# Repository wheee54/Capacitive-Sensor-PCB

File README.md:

# Capacitive-Sensor-PCB
Demo Project for NUS Shape of Sound Class

This project is based on the (1) USBMIDI library for Arduino by Blokas [Link: https://github.com/BlokasLabs/USBMIDI] and (2) Electronics as Material Touch Sensor example by clementzheng [Link: https://github.com/clementzheng/Electronics-As-Material]

## Hardware

The dreamer nano microcontroller [Link: https://www.dfrobot.com/product-786.html] is used as a midi device and needs to be connected to a VST via USB.
The PCB files have headers for the microcontoller and also features a built in touch sensor into the top copper layer.

## Code

The .h files required should be downloaded before use.
It is recommended to uncomment the Serial.print lines to read and tune capVal for your specific design.

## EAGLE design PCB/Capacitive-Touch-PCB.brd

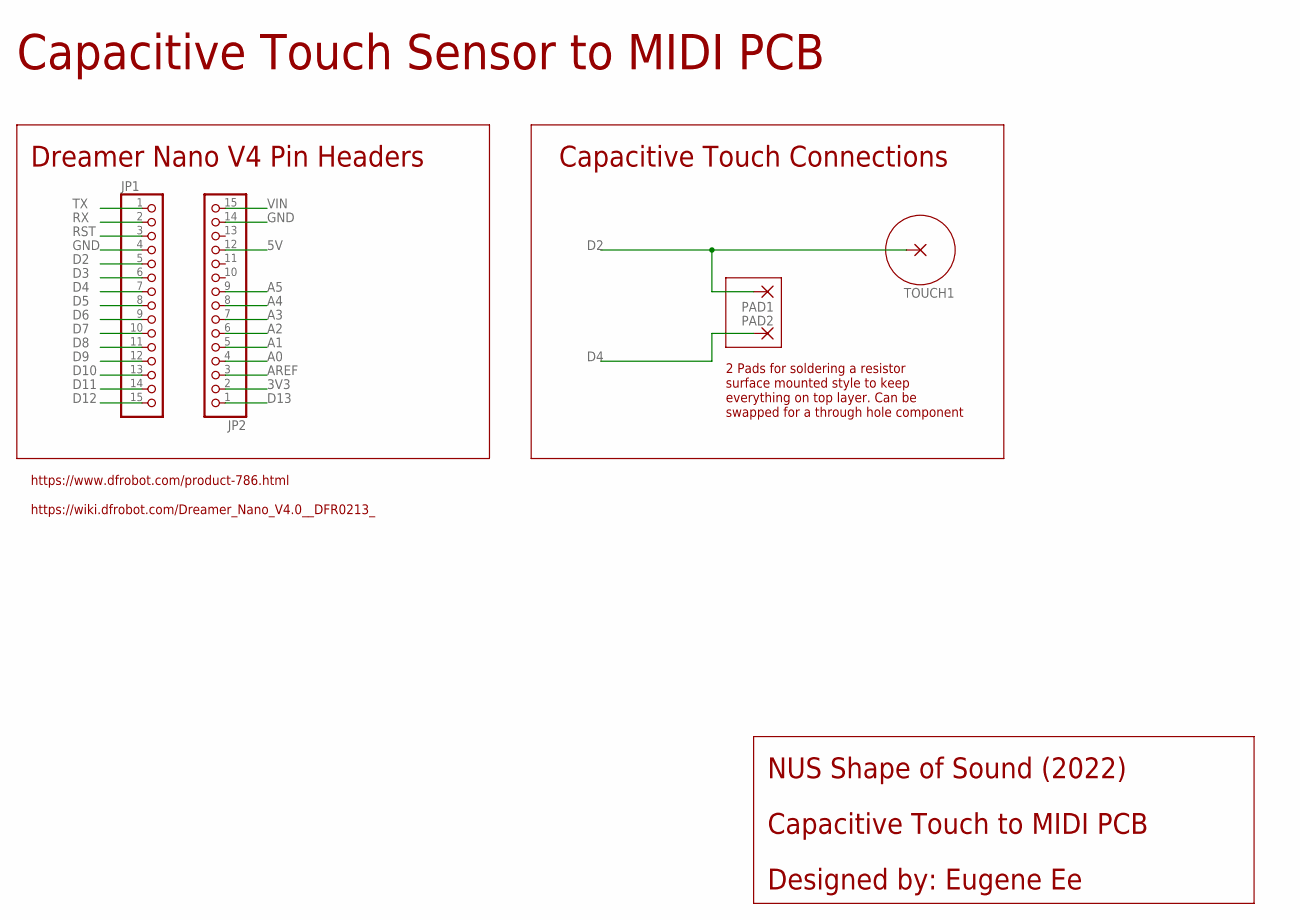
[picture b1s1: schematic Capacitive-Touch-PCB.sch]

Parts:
JP1, JP2: PINHD-1X15; 1X15
PAD1, PAD2: SMD5; SMD2,54-5,08
TOUCH1: SMD5; SMD2,54-5,08

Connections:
3V3: JP2.2
5V: JP2.12
A0: JP2.4
A1: JP2.5
A2: JP2.6
A3: JP2.7
A4: JP2.8
A5: JP2.9
AREF: JP2.3
D2: JP1.5, PAD1.1, TOUCH1.1
D3: JP1.6
D4: JP1.7, PAD2.1
D5: JP1.8
D6: JP1.9
D7: JP1.10
D8: JP1.11
D9: JP1.12
D10: JP1.13
D11: JP1.14
D12: JP1.15
D13: JP2.1
GND: JP1.4, JP2.14
RST: JP1.3
RX: JP1.2
TX: JP1.1
VIN: JP2.15

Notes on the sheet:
Dreamer Nano V4 Pin Headers
Capacitive Touch Sensor to MIDI PCB
2 Pads for soldering a resistor surface mounted style to keep everything on top layer. Can be swapped for a through hole component
Capacitive Touch Connections
Capacitive Touch to MIDI PCB
Designed by: Eugene Ee
NUS Shape of Sound (2022)
https://www.dfrobot.com/product-786.html https://wiki.dfrobot.com/Dreamer_Nano_V4.0__DFR0213_

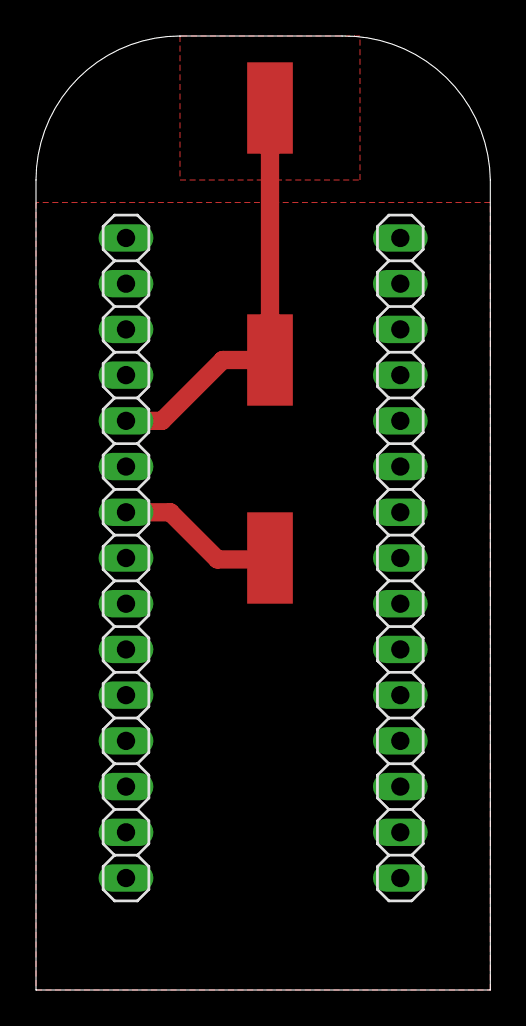
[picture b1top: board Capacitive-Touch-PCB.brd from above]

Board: 2 copper layers, 25.2 x 53.0 mm, 5 parts (0 on the bottom side), 3 nets.

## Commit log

2022-09-09 Create code
2022-09-09 Add Arduino Code
2022-09-09 Arduino Code
2022-09-09 PCB files
